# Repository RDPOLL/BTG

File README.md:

BTG  - Batterie Test Gerät

This is to test Battery packs under predefined current, if they reach a certain voltage.

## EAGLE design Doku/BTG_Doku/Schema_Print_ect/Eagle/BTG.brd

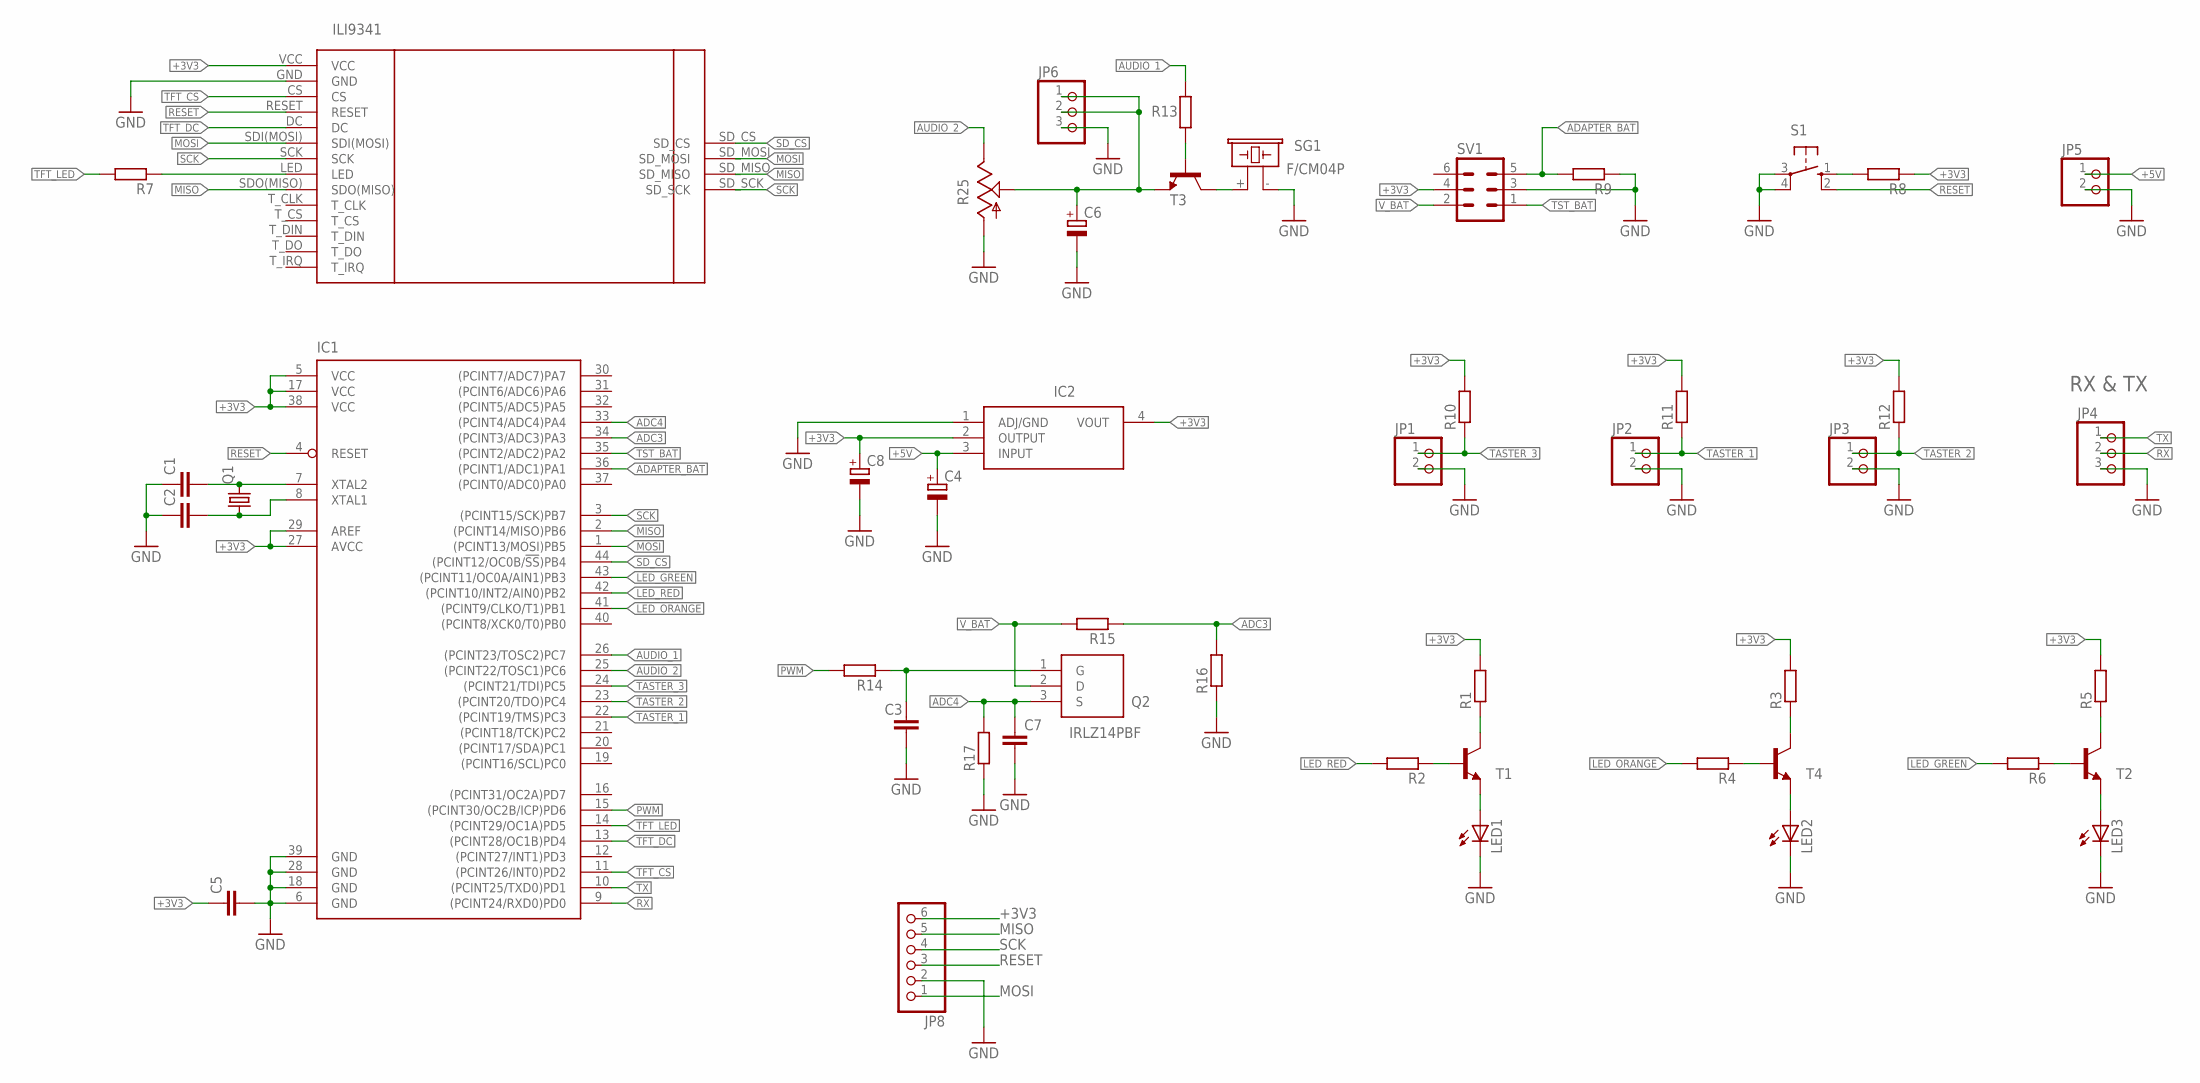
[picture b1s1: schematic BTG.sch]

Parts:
C1, C2, C3: C-EU025-024X044; C025-024X044
C4, C8: CPOL-EUSMCB; SMC_B
C5, C7: C-EU050-025X075; C050-025X075
C6: CPOL-EUE2,5-6E; E2,5-6E
IC1: ATMEGA644A; TQFP44
IC2: LMS8117AMP-3.3_NOPB; SOT230P700X180-4N
JP1, JP2, JP3, JP5: PINHD-1X2; 1X02
JP4, JP6: PINHD-1X3; 1X03
JP8: PINHD-1X6; 1X06
LED1, LED2, LED3: LED5MM
Q1: CRYSTALHC49U-V; HC49U-V
Q2: IRLZ14PBF; TO254P465X1031X1954-3P
R1, R2, R3, R4, R5, R6, R7, R8, R9, R10, R11, R12, R13, R14, R15, R16, R17: R-EU_0204/7; 0204/7
R25: TRIM_US-LI15; LI15
S1: 10-XX; B3F-10XX
SG1: F/CM04P
SV1: ML6L
T1, T2, T3, T4: 2N3904; TO92
U$1: ILI9341

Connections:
+3V3: C5.1, C8.+, IC1.5 (VCC), IC1.17 (VCC), IC1.27 (AVCC), IC1.29 (AREF), IC1.38 (VCC), IC2.2 (OUTPUT), IC2.4 (VOUT), JP8.6, R1.2, R3.2, R5.2, R8.1, R10.2, R11.2, R12.2, SV1.4, U$1.VCC
+5V: C4.+, IC2.3 (INPUT), JP5.1
ADAPTER_BAT: IC1.36 ((PCINT1/ADC1)PA1), R9.2, SV1.5
ADC3: IC1.34 ((PCINT3/ADC3)PA3), R15.1, R16.2
ADC4: C7.1, IC1.33 ((PCINT4/ADC4)PA4), Q2.3 (S), R17.2
AUDIO_1: IC1.26 ((PCINT23/TOSC2)PC7), R13.2
AUDIO_2: IC1.25 ((PCINT22/TOSC1)PC6), R25.E
GND: C1.1, C2.1, C3.2, C4.-, C5.2, C6.-, C7.2, C8.-, IC1.6 (GND), IC1.18 (GND), IC1.28 (GND), IC1.39 (GND), IC2.1 (ADJ/GND), JP1.2, JP2.2, JP3.2, JP4.3, JP5.2, JP6.3, JP8.2, LED1.K (C), LED2.K (C), LED3.K (C), R9.1, R16.1, R17.1, R25.A, S1.3, S1.4 (P1), SG1.- (2), SV1.3, U$1.GND
LED_GREEN: IC1.43 ((PCINT11/OC0A/AIN1)PB3), R6.2
LED_ORANGE: IC1.41 ((PCINT9/CLKO/T1)PB1), R4.2
LED_RED: IC1.42 ((PCINT10/INT2/AIN0)PB2), R2.2
MISO: IC1.2 ((PCINT14/MISO)PB6), JP8.5, U$1.SDO(MISO), U$1.SD_MISO
MOSI: IC1.1 ((PCINT13/MOSI)PB5), JP8.1, U$1.SDI(MOSI), U$1.SD_MOSI
unnamed: R1.1, T1.1 (C)
unnamed: R2.1, T1.2 (B)
unnamed: LED1.A, T1.3 (E)
unnamed: LED2.A, T4.3 (E)
unnamed: R4.1, T4.2 (B)
unnamed: R3.1, T4.1 (C)
unnamed: R5.1, T2.1 (C)
unnamed: R6.1, T2.2 (B)
unnamed: LED3.A, T2.3 (E)
unnamed: R7.1, U$1.LED
unnamed: C1.2, IC1.7 (XTAL2), Q1.2
unnamed: R8.2, S1.1 (S)
unnamed: R13.1, T3.2 (B)
unnamed: SG1.+ (1), T3.1 (C)
unnamed: C2.2, IC1.8 (XTAL1), Q1.1
unnamed: C6.+, JP6.1, JP6.2, R25.S, T3.3 (E)
unnamed: C3.1, Q2.1 (G), R14.1
PWM: IC1.15 ((PCINT30/OC2B/ICP)PD6), R14.2
RESET: IC1.4 (RESET), JP8.3, S1.2 (S1), U$1.RESET
RX: IC1.9 ((PCINT24/RXD0)PD0), JP4.2
SCK: IC1.3 ((PCINT15/SCK)PB7), JP8.4, U$1.SCK, U$1.SD_SCK
SD_CS: IC1.44 ((PCINT12/OC0B/!SS!)PB4), U$1.SD_CS
TASTER_1: IC1.22 ((PCINT19/TMS)PC3), JP2.1, R11.1
TASTER_2: IC1.23 ((PCINT20/TDO)PC4), JP3.1, R12.1
TASTER_3: IC1.24 ((PCINT21/TDI)PC5), JP1.1, R10.1
TFT_CS: IC1.11 ((PCINT26/INT0)PD2), U$1.CS
TFT_DC: IC1.13 ((PCINT28/OC1B)PD4), U$1.DC
TFT_LED: IC1.14 ((PCINT29/OC1A)PD5), R7.2
TST_BAT: IC1.35 ((PCINT2/ADC2)PA2), SV1.1
TX: IC1.10 ((PCINT25/TXD0)PD1), JP4.1
V_BAT: Q2.2 (D), R15.2, SV1.2

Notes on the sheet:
RX & TX

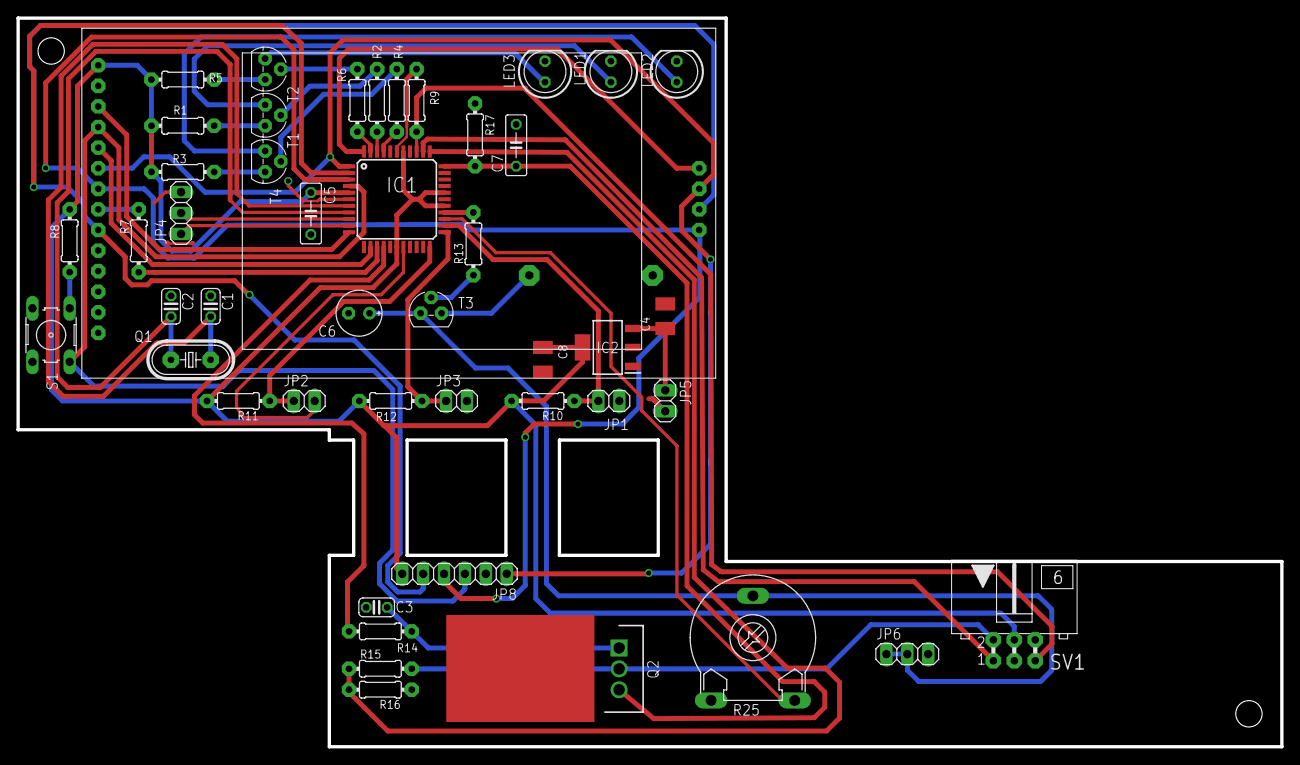
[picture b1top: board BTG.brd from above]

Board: 2 copper layers, 153.5 x 88.5 mm, 48 parts (1 on the bottom side), 44 nets.

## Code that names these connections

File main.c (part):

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//gray background for display
#define BACK_GRAY (LCD_RGB(32,32,32))

#define LED_ORA_ON      PORTB|= (1<<PB1)
#define LED_ORA_OFF		PORTB &= ~(1<<PB1)
#define LED_ROT_ON		PORTB |= (1<<PB2)
#define LED_ROT_OFF		PORTB &= ~(1<<PB2)
#define LED_GRUN_ON		PORTB |= (1<<PB3)
#define LED_GRUN_OFF	PORTB &= ~(1<<PB3)

#define TRANSISTOR_OFF	PORTC &= ~(1<<PC7)
#define TRANSISTOR_ON	PORTC |= (1<<PC7)

#define PIEZZO_OFF		PORTC &= ~((1<<PC6)| (1<<PC7))
#define PIEZZO_ON		PORTC |= ((1<<PC6) | (1<<PC7))
#define LED_BAT_ON		PORTD |= (1<<PD0)
#define LED_BAT_OFF		PORTD &= ~(1<<PD0)

#define linearOffset 0		//Offset in mA
#define gainOffset 260		//Gainoffset for current measurement
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    FIL fil;
    int stat;
  
	DDRD |= (1<<PD5);
	PORTD |= (1<<PD5);			//LED Display
	
	DDRB |= (1<<PB4);
	PORTB |= (1<<PB4);			//SD-Karte; CS
	
	DDRD |= (1<<PD0);
	PORTD &= ~(1<<PD0);			//LED Bat
	
	DDRB |= (1<<PB2);
	PORTB &= ~(1<<PB2);			//LED Rot
	
	DDRB |= (1<<PB3);
	PORTB &= ~(1<<PB3);			//LED Grün
	
	DDRC |= (1<<PC7);
	PORTC &= ~(1<<PC7);			//Transistor
	
	DDRC |= (1<<PC6);
	PORTC &= ~(1<<PC6);			//Piezzo
	
	DDRC &= ~(1<<PC4);
	PORTC |= (1<<PC4);			//ENTER-Taster
	
	DDRC &= ~(1<<PC3);
	PORTC |= (1<<PC3);			//DOWN-Taster
	
	DDRC &= ~(1<<PC5);
	PORTC |= (1<<PC5);			//UP-Taster
	
	DDRA &= ~(1<<PA2);
	PORTA &= ~(1<<PA2);			//Taster im Adapter
	
	DDRA &= ~(1<<PA1);
	PORTA &= ~(1<<PA1);			//Adaptererkennung
	
	DDRD |= (1<<PD6);

	DDRD |= (1<<PD1);
	//^tx
	
	/* Start 100Hz system timer with TC0 */
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
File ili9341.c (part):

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
void ili9341_spi_init(void)//set spi speed and settings
{
DDRB |=  (1<<PB4) | (1<<PB5) | (1<<PB7);//CS,SS,MOSI,SCK as output(although SS will be unused throughout the program)
DDRB &= ~(1<<PB6);
 SPCR=(1<<SPE) | (1<<MSTR);// | (1<<SPR0);//mode 0,fosc/4
SPSR |=(1<<SPI2X);//doubling spi speed.i.e final spi speed-fosc/2
PORTD |= (1<<PD2);//cs off during startup

}

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
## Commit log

2020-10-09 first
2020-10-09 all c header files
2020-10-09 small changes
2020-10-18 Changes to be committed: modified: Makefile modified: ili9341.c modified: ili9341.h modified: main.c
2020-10-21 modified: ili9341.c modified: ili9341.h modified: main.c
2020-10-22 Clean Up
2020-10-22 analog
2020-10-22 Remove unneeded file ..
    deleted: byteordering.c
    deleted: byteordering.h
    deleted: byteordering.o
2020-10-22 More cleanup, moved F_CPU to makefile so all delay.h are ok. Changes with adc -> include adc.h not adc.c Changes to keep gcc happy about declarations.
    modified: ADC.c
    modified: Makefile
    new file: adc.h
    modified: ili9341.c
    modified: main.c
2020-10-22 Consistent F_CPU (uart.c had a wrong definition ) now F_CPU only in Makefile change !!! More cleanup to keep gcc happy.
    modified: ili9341.c
    modified: uart.c
2020-10-23 some more clean up (I2C removed)
2020-10-25 added chan's fatfs for sd support clean up will be needed as there are too many files. For now everything is added.
    modified: main.c
    modified: uart.c
2020-10-28 Modification due to adc conversations.
    modified: main.c
2020-10-28 added comment to "read.ini" stuff and remove debug stuff from fatfs modified: fatfs/ff.c modified: main.c
2020-10-30 doku
2020-10-31 Added doc dir, added icons for graphics, added write support, put ifdef around uneeded function to make smaller image.
    new file: Achtung.h
    modified: Makefile
    new file: Stop.h
    new file: doc/cur.dat
    new file: doc/main.png
    new file: doc/prg_flow.dot
2020-10-31 Cleanup for end user, added "failed"/"passed" field in csv. Now the display changes when batery failes or passes.
    modified: README.md
    modified: main.c
2020-10-31 Forgat Volt.h new file: Volt.h
2020-11-01 made chages to Makefiles to simplify linking ... now it checks also the fatfs makefile and creates the archive file. modified: Makefile modified: fatfs/Makefile_mmc
2020-11-05 Forgat Gear.h to add. new file: Gear.h modified: Makefile modified: main.c
2020-11-05 msg box fix
2020-11-05 Added delay after power up SD Card... just to relax time for the card modified: fatfs/mmc_avr_spi.c
2020-11-05 schema
2020-11-05 increased delay after power on... SD Specifications say up to 35ms .. so increased it to 100ms modified: fatfs/mmc_avr_spi.c
2020-11-05 Forgat add PROGMEM in Gear.h And.. Fixed SD Card Proble @ powerup. Looks like some Cards need more time or clk cycles to fully start.. So there is now a retry_cnt, if initialisation fail first, it tr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
2020-11-06 SD init
2020-11-06 logo corrections
2020-11-12 Text fixed
2020-11-13 some clean up
2020-11-18 Fixed Textsize
2020-11-19 Added origin of the files modified: Doku/Doku-BTG.docx
2020-11-19 ADDED git history new file: LOG
2020-11-25 commentary added
2020-11-27 added comment modified: Doku/Doku-BTG.docx modified: main.c
2020-12-02 added Doku
2020-12-03 Doku updated
2020-12-03 doku finished
